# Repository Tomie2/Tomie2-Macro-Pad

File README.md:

# Tomie2-Macro-Pad
My very first keyboard PCB!

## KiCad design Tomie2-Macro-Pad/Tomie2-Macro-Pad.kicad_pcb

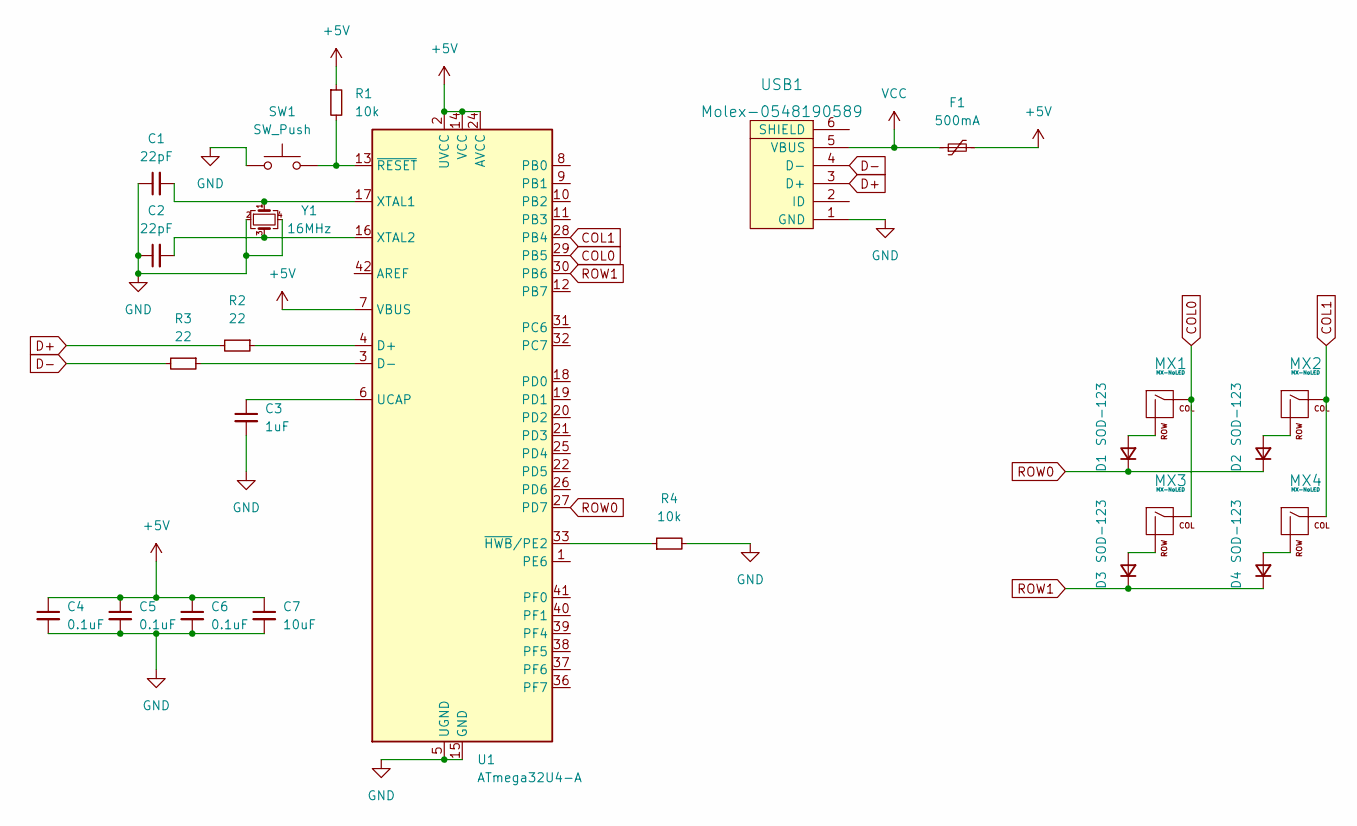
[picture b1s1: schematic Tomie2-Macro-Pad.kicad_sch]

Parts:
C1, C2: 22pF; C_0805_2012Metric
C3: 1uF; C_0805_2012Metric
C4, C5, C6: 0.1uF; C_0805_2012Metric
C7: 10uF; C_0805_2012Metric
D1, D2, D3, D4: SOD-123; D_SOD-123
F1: 500mA; Fuse_1206_3216Metric
MX1, MX2, MX3, MX4: MX-NoLED; MXOnly-1U-NoLED
R1, R4: 10k; R_0805_2012Metric
R2, R3: 22; R_0805_2012Metric
SW1: SW_Push; SKQG-1155865
U1: ATmega32U4-A; TQFP-44_10x10mm_P0.8mm
USB1: Molex-0548190589
Y1: 16MHz; Crystal_SMD_3225-4Pin_3.2x2.5mm

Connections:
+5V: C4.1, C5.1, C6.1, C7.1, F1.2, R1.1, U1.2 (UVCC), U1.7 (VBUS), U1.14 (VCC), U1.24 (AVCC), U1.34 (VCC), U1.44 (AVCC)
COL0: MX1.1 (COL), MX3.1 (COL), U1.29 (PB5)
COL1: MX2.1 (COL), MX4.1 (COL), U1.28 (PB4)
D+: R2.2, USB1.3 (D+)
D-: R3.2, USB1.4 (D-)
GND: C1.1, C2.1, C3.2, C4.2, C5.2, C6.2, C7.2, R4.2, SW1.1, U1.5 (UGND), U1.15 (GND), U1.23 (GND), U1.35 (GND), U1.43 (GND), USB1.1 (GND), Y1.2, Y1.4
unnamed: C1.2, U1.17 (XTAL1), Y1.1
unnamed: C2.2, U1.16 (XTAL2), Y1.3
unnamed: C3.1, U1.6 (UCAP)
unnamed: D1.2 (A), MX1.2 (ROW)
unnamed: D2.2 (A), MX2.2 (ROW)
unnamed: D3.2 (A), MX3.2 (ROW)
unnamed: D4.2 (A), MX4.2 (ROW)
unnamed: R1.2, SW1.2, U1.13 (~RESET)
unnamed: R2.1, U1.4 (D+)
unnamed: R3.1, U1.3 (D-)
unnamed: R4.1, U1.33 (~HWB/PE2)
ROW0: D1.1 (K), D2.1 (K), U1.27 (PD7)
ROW1: D3.1 (K), D4.1 (K), U1.30 (PB6)
VCC: F1.1, USB1.5 (VBUS)

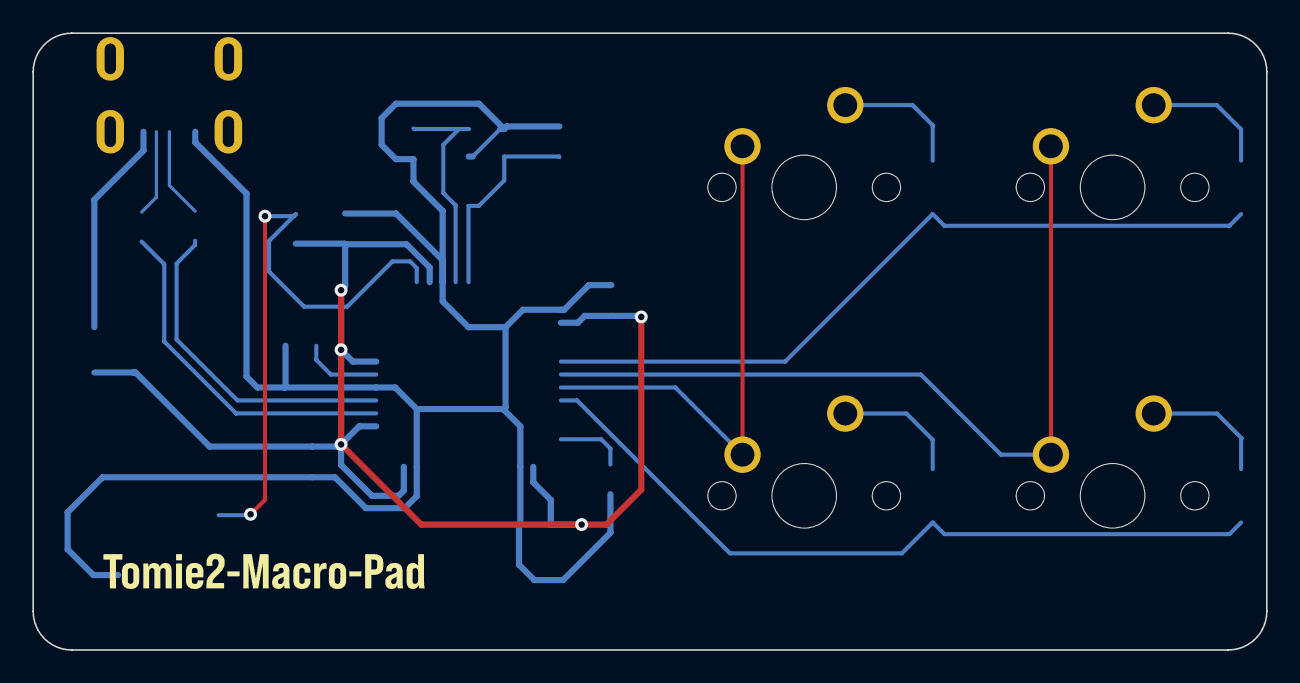
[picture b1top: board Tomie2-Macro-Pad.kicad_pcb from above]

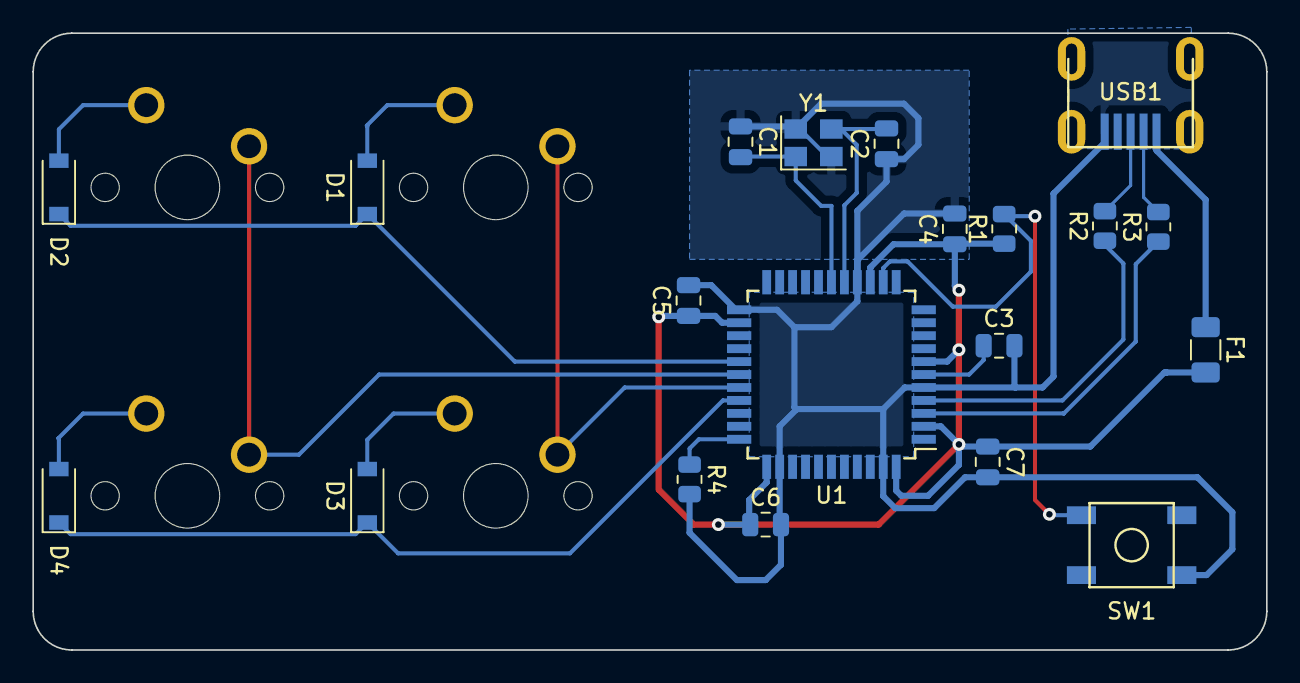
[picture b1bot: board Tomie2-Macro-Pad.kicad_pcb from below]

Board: 2 copper layers, 76.2 x 38.1 mm, 24 parts (20 on the bottom side), 20 nets.

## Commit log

2022-11-08 Initialize Project
2022-11-08 Add submodules
2022-11-08 Add footprint libraries
2022-11-08 MCU Schematic Created
2022-11-09 Schematic Complete
2022-11-09 PCB Progress
2022-11-11 PCB Finished
2022-11-11 Added PCB Render
2022-11-11 Relocated PCB render
